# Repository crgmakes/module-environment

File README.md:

# Aquarius Environment Module

Environment monitoring module. Temperature, light, VOC, NOX, etc.

# Software 

You will need [KiCad](https://kicad.org) to view and edit this design. Click [here](https://www.kicad.org/download/) to download.

You will also need all the associated libraries and models to drive the design if you want to make changes or view the 3D rendering:

https://github.com/crgmakes/kicad-library.git

Kicad MUST be configured properly to use all the files in this repo. Once you have Kicad installed, under Preferences->Configure Paths..., make the following entries:

1 - KICAD_USER_DIR -> set to the root location of where you placed the above repository.
2 - KICAD_USER_LIBRARY = ${KICAD_USER_DIR}/Library
3 - KICAD_USER_MODEL_DIR = ${KICAD_USER_LIBRARY}/models
4 - KICAD_USER_TEMPLATE_DIR	= ${KICAD_USER_LIBRARY}/templates	

Kicad will operate mostly normally if these are not set properly. You will notice an issue when you view the PCB in 3D mode.

***NOTE***: after makeing a release build in git, if your rendered 3D images are missing components, ensure the path to EVERY component model is set to ${KICAD_USER_MODEL_DIR}/<model name>.

Kicad sometimes replaces the variable with an expansion and that FAILS during the build process because the expanded variable is local and does not match the build environment.

---

THE DESIGN IS PROVIDED "AS IS" AND THE AUTHOR DISCLAIMS ALL WARRANTIES WITH REGARD TO THIS DESIGN INCLUDING ALL IMPLIED WARRANTIES OF MERCHANTABILITY AND FITNESS. IN NO EVENT SHALL THE AUTHOR BE LIABLE FOR ANY SPECIAL, DIRECT, INDIRECT, OR CONSEQUENTIAL DAMAGES OR ANY DAMAGES WHATSOEVER RESULTING FROM LOSS OF USE, DATA OR PROFITS, WHETHER IN AN ACTION OF CONTRACT, NEGLIGENCE OR OTHER TORTIOUS ACTION, ARISING OUT OF OR IN CONNECTION WITH THE USE OR PERFORMANCE OF THIS DESIGN.

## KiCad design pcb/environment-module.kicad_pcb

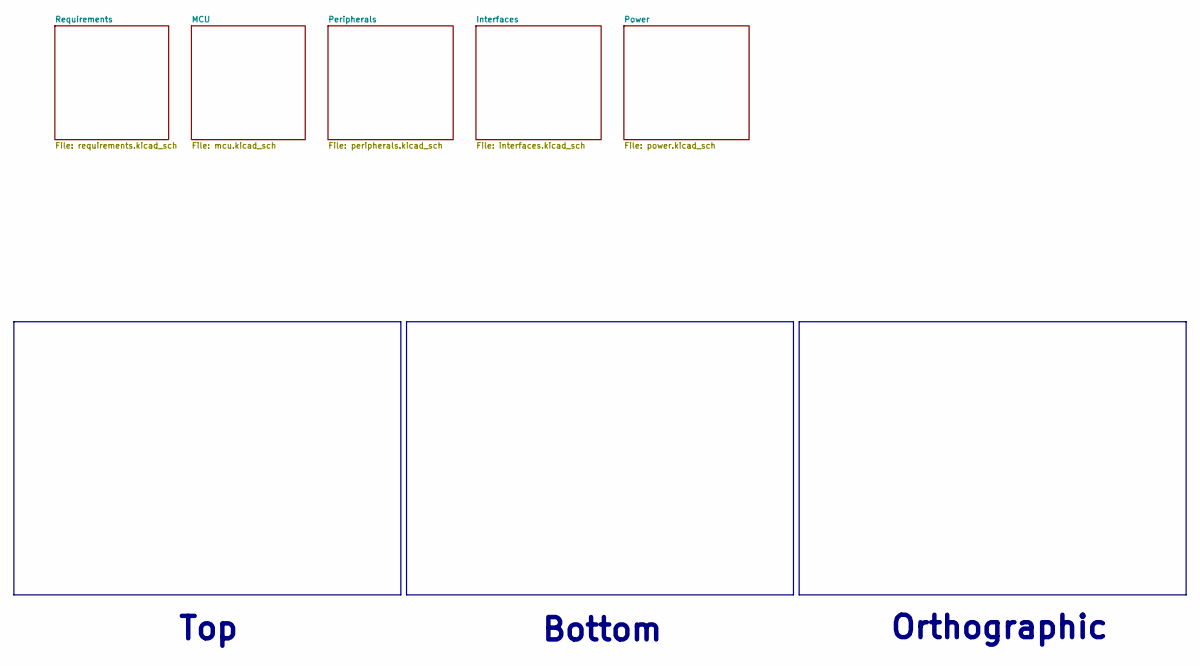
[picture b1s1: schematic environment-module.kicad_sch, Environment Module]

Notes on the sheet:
Bottom
Top
Orthographic

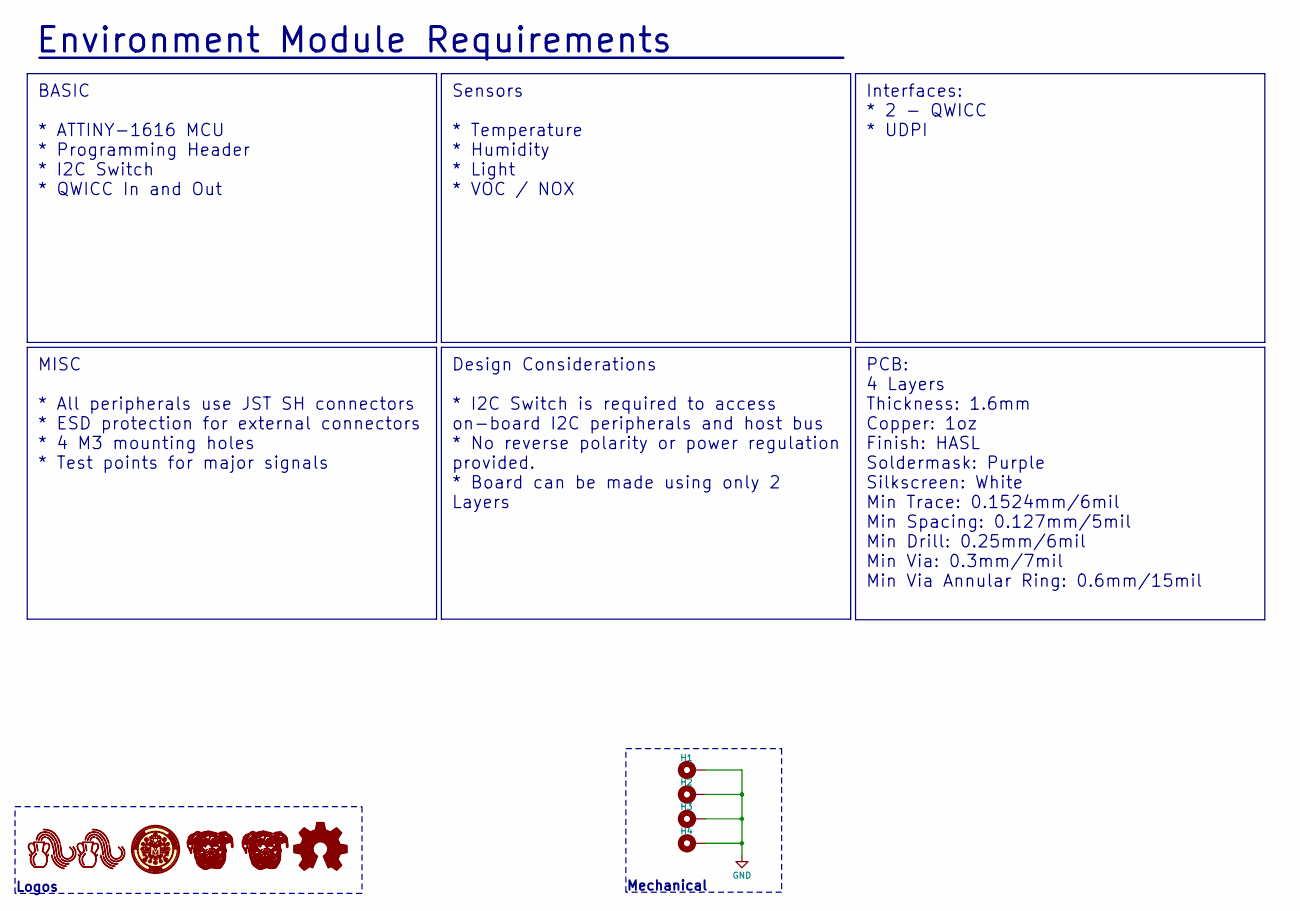
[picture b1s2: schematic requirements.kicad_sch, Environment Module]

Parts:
H1, H2, H3, H4: MountingHole_3.2mm_M3_Pad_Via
LOGO1, LOGO2: Aquarius Logo 5mm
LOGO3: CRGM Logo 7mm
LOGO4, LOGO5: Roxy 6.5mm
LOGO6: OSHW-Logo_5.7x6mm_SilkScreen

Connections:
GND: H1.1, H2.1, H3.1, H4.1; also elsewhere on the board

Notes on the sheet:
Logos
Environment Module Requirements
Mechanical
Interfaces: * 2 - QWICC * UDPI
PCB: 4 Layers Thickness: 1.6mm Copper: 1oz Finish: HASL Soldermask: Purple Silkscreen: White Min Trace: 0.1524mm/6mil Min Spacing: 0.127mm/5mil Min Drill: 0.25mm/6mil Min Via: 0.3mm/7mil Min Via Annular Ring: 0.6mm/15mil
BASIC * ATTINY-1616 MCU * Programming Header * I2C Switch * QWICC In and Out
MISC * All peripherals use JST SH connectors * ESD protection for external connectors * 4 M3 mounting holes * Test points for major signals
Sensors * Temperature * Humidity * Light * VOC / NOX
Design Considerations * I2C Switch is required to access on-board I2C peripherals and host bus * No reverse polarity or power regulation provided. * Board can be made using only 2 Layers

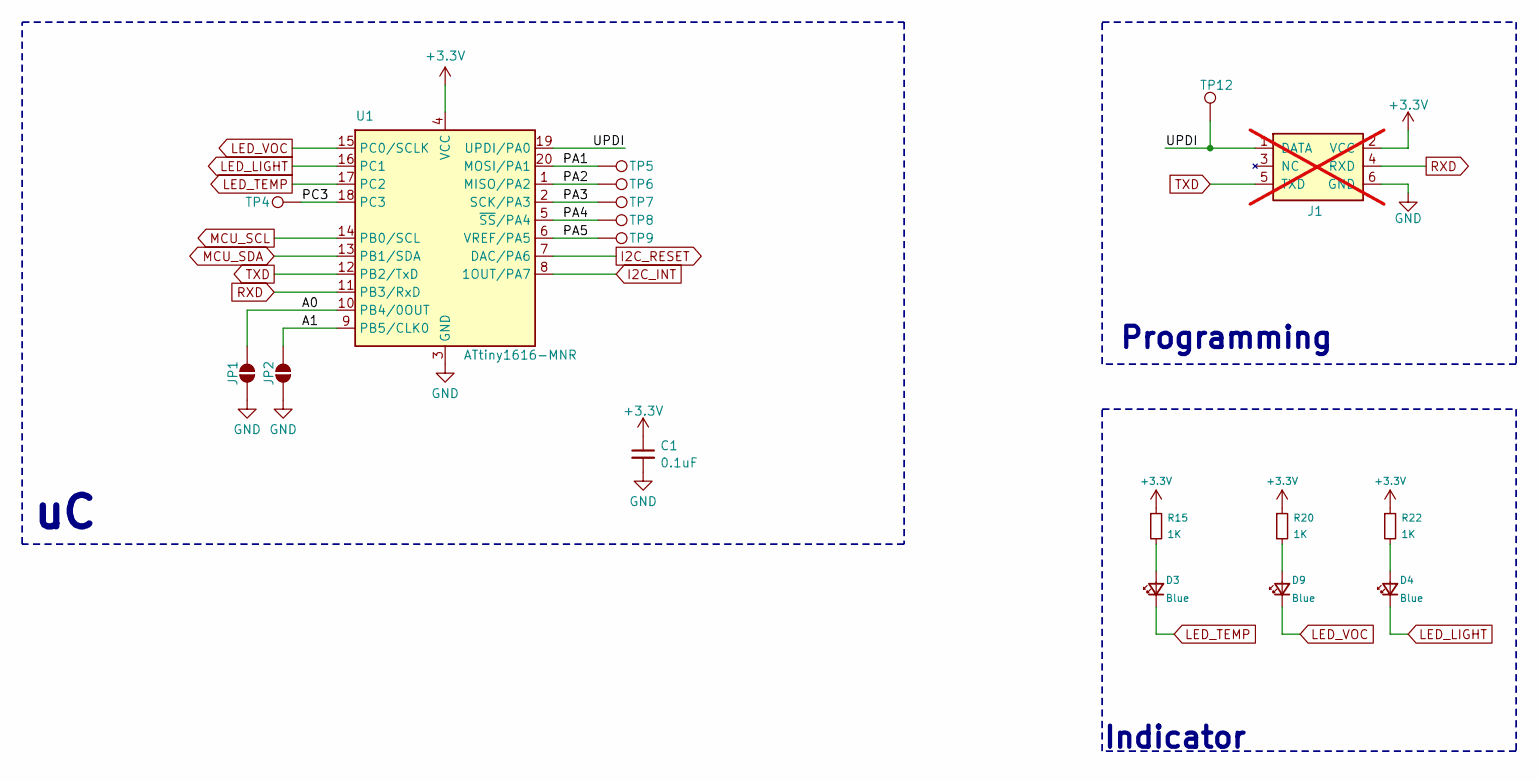
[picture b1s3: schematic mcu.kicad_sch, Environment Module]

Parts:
C1: 0.1uF; C_0603_1608Metric; Tolerance 10%; MPN CL10B104KO8NNNC; LCSC C66501
D3, D4, D9: Blue; LED_0603_1608Metric; MPN XL-1608UBC-04; Mouser 859-LTST-C190TBKT
J1: AVR-UPDI-6; PinHeader_2x03_P2.54mm_Vertical_SMD; not fitted
JP1, JP2: SolderJumper-2_P1.3mm_Open_RoundedPad1.0x1.5mm
R15, R20, R22: 1K; R_0603_1608Metric; Tolerance 5%; MPN FRC0603J102 TS; Mouser 71-CRCW06031K00JNEAC
TP4, TP5, TP6, TP7, TP8, TP9, TP12: TestPoint_Pad_D1.0mm
U1: ATtiny1616-MNR; VQFN-20-1EP_3x3mm_P0.4mm_EP1.7x1.7mm_ThermalVias; MPN ATTINY1616-MNR; Mouser 556-ATTINY1616MNR

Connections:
+3.3V: C1.1, J1.2 (VCC), R15.1, R20.1, R22.1, U1.4 (VCC); also elsewhere on the board
/MCU/A0: JP1.2 (B), U1.10 (PB4/0OUT)
/MCU/A1: JP2.2 (B), U1.9 (PB5/CLK0)
/MCU/PA1: TP5.1, U1.20 (MOSI/PA1)
/MCU/PA2: TP6.1, U1.1 (MISO/PA2)
/MCU/PA3: TP7.1, U1.2 (SCK/PA3)
/MCU/PA4: TP8.1, U1.5 (~SS/PA4)
/MCU/PA5: TP9.1, U1.6 (VREF/PA5)
/MCU/PC3: TP4.1, U1.18 (PC3)
/MCU/UPDI: J1.1 (DATA), TP12.1, U1.19 (UPDI/PA0)
GND: C1.2, J1.6 (GND), JP1.1 (A), JP2.1 (A), U1.3 (GND), U1.21 (GND); also elsewhere on the board
I2C_INT: U1.8 (1OUT/PA7); also elsewhere on the board
I2C_RESET: U1.7 (DAC/PA6); also elsewhere on the board
LED_LIGHT: D4.1 (K), U1.16 (PC1)
LED_TEMP: D3.1 (K), U1.17 (PC2)
LED_VOC: D9.1 (K), U1.15 (PC0/SCLK)
MCU_SCL: U1.14 (PB0/SCL); also elsewhere on the board
MCU_SDA: U1.13 (PB1/SDA); also elsewhere on the board
unnamed: D3.2 (A), R15.2
unnamed: D4.2 (A), R22.2
unnamed: D9.2 (A), R20.2
RXD: J1.4 (RXD), U1.11 (PB3/RxD)
TXD: J1.5 (TXD), U1.12 (PB2/TxD)

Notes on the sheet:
Programming
Indicator

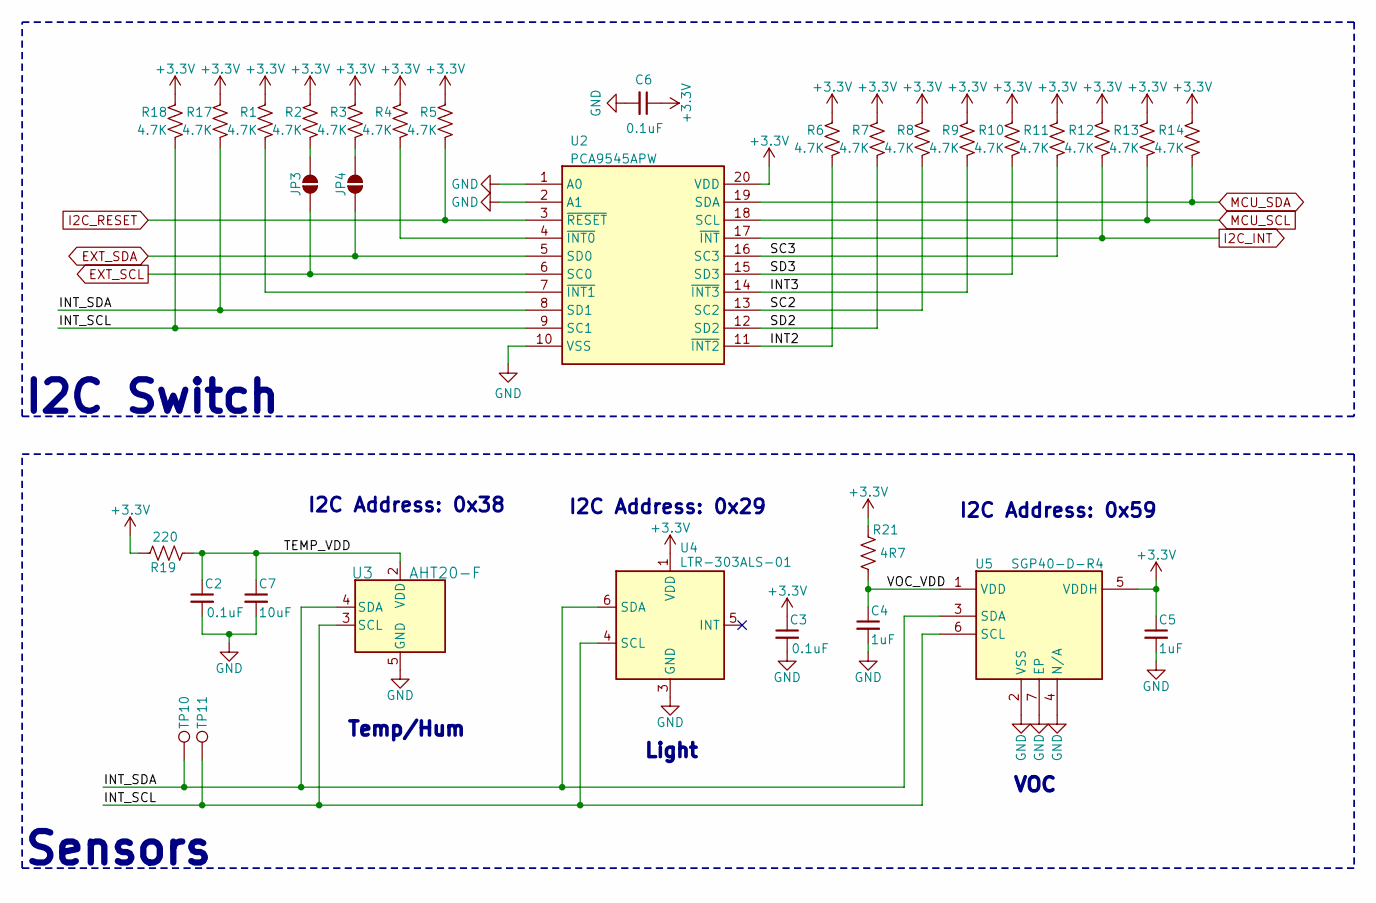
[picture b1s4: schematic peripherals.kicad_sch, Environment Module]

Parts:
C2, C3: 0.1uF; C_0603_1608Metric; Tolerance 10%; MPN CL10B104KO8NNNC; Digikey 1276-1005-2-ND
C4, C5: 1uF; C_0603_1608Metric; Tolerance 10%; MPN CGA0603X5R105K160JT; Mouser 187-CL10B105KO8NNNC
C6: 0.1uF; C_0603_1608Metric; Tolerance 10%; MPN CL10B104KO8NNNC; LCSC C66501
C7: 10uF; C_0603_1608Metric; Tolerance 10%; MPN CGA0603X5R106K100JT; Mouser 187-CL10A106KP8NNNC
JP3, JP4: SolderJumper-2_P1.3mm_Open_RoundedPad1.0x1.5mm
R1, R2, R3, R4, R5, R6, R7, R9, R10, R12, R13, R17, R18: 4.7K; R_0603_1608Metric; Tolerance 5%; MPN FRC0603J472 TS; Mouser 71-CRCW06034K70JNEAC
R8, R11, R14: 4.7K; R_0603_1608Metric; Tolerance 5%; MPN FRC0603J472 TS; LCSC C2907166
R19: 220; R_0603_1608Metric; Tolerance 5%; MPN FRC0603J221 TS; Mouser 652-CR0603JW-221ELF
R21: 4R7; R_0603_1608Metric; Tolerance 5%; MPN FRC0603J4R7 TS; Mouser 652-CR0603JW-4R7ELF
TP10, TP11: TestPoint_Pad_D1.0mm
U2: PCA9545APW; SOP65P640X110-20N; MPN PCA9545APW,118; Digikey 568-1865-2-ND
U3: AHT20-F; AHT20; MPN AHT20-F; LCSC C3012622
U4: LTR-303ALS-01; MPN LTR-303ALS-01; Digikey 160-2161-2-ND
U5: SGP40-D-R4; SON80P244X244X95-7N; MPN SGP40-D-R4; Digikey 1649-SGP40-D-R4TR-ND

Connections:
+3.3V: C3.1, C5.1, C6.1, R1.2, R2.2, R3.2, R4.2, R5.2, R6.2, R7.2, R8.2, R9.2, R10.2, R11.2, R12.2, R13.2, R14.2, R17.2, R18.2, R19.1, R21.1, U2.20 (VDD), U4.1 (VDD), U5.5 (VDDH); also elsewhere on the board
/Peripherals/INT2: R6.1, U2.11 (~INT2)
/Peripherals/INT3: R9.1, U2.14 (~INT3)
/Peripherals/INT_SCL: R18.1, TP11.1, U2.9 (SC1), U3.3 (SCL), U4.4 (SCL), U5.6 (SCL)
/Peripherals/INT_SDA: R17.1, TP10.1, U2.8 (SD1), U3.4 (SDA), U4.6 (SDA), U5.3 (SDA)
/Peripherals/SC2: R8.1, U2.13 (SC2)
/Peripherals/SC3: R11.1, U2.16 (SC3)
/Peripherals/SD2: R7.1, U2.12 (SD2)
/Peripherals/SD3: R10.1, U2.15 (SD3)
/Peripherals/TEMP_VDD: C2.1, C7.1, R19.2, U3.2 (VDD)
/Peripherals/VOC_VDD: C4.1, R21.2, U5.1 (VDD)
EXT_SCL: JP3.1 (A), U2.6 (SC0); also elsewhere on the board
EXT_SDA: JP4.1 (A), U2.5 (SD0); also elsewhere on the board
GND: C2.2, C3.2, C4.2, C5.2, C6.2, C7.2, U2.1 (A0), U2.2 (A1), U2.10 (VSS), U3.5 (GND), U4.3 (GND), U5.2 (VSS), U5.4 (N/A), U5.7 (EP); also elsewhere on the board
I2C_INT: R12.1, U2.17 (~INT); also elsewhere on the board
I2C_RESET: R5.1, U2.3 (~RESET); also elsewhere on the board
MCU_SCL: R13.1, U2.18 (SCL); also elsewhere on the board
MCU_SDA: R14.1, U2.19 (SDA); also elsewhere on the board
unnamed: JP3.2 (B), R2.1
unnamed: JP4.2 (B), R3.1
unnamed: R4.1, U2.4 (~INT0)
unnamed: R1.1, U2.7 (~INT1)

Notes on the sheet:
I2C Address: 0x29
I2C Address: 0x59
Light
Sensors
VOC
Temp/Hum
I2C Switch
I2C Address: 0x38

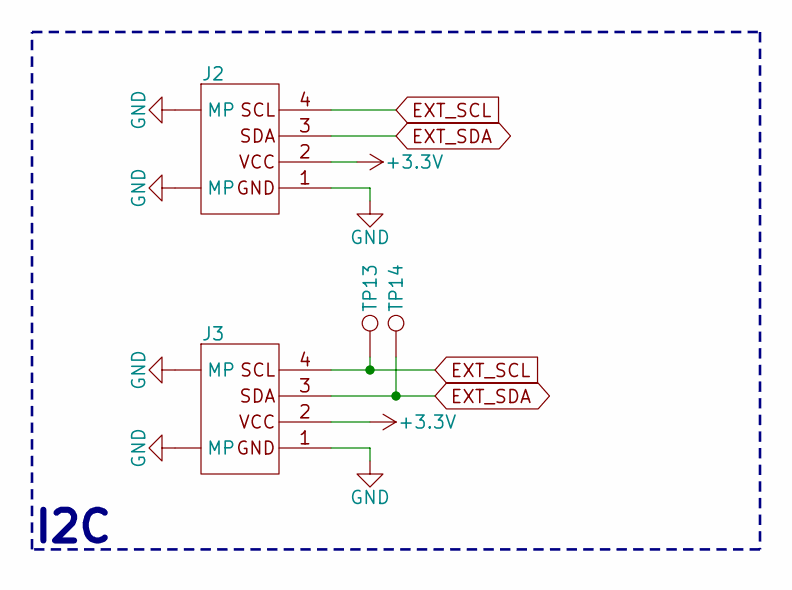
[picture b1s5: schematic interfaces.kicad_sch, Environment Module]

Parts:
J2, J3: JST_SH_BM04B-SRSS-TB_1x04-1MP_P1.00mm_Vertical; MPN BM04B-SRSS-TBT(LF)(SN); Mouser 306-BM04BSRSSTBTLFSN
TP13, TP14: TestPoint_Pad_D1.0mm

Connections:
+3.3V: J2.2, J3.2; also elsewhere on the board
EXT_SCL: J2.4, J3.4, TP13.1; also elsewhere on the board
EXT_SDA: J2.3, J3.3, TP14.1; also elsewhere on the board
GND: J2.0 (MP), J2.1, J2.5 (MP), J3.0 (MP), J3.1, J3.5 (MP); also elsewhere on the board

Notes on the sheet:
I2C

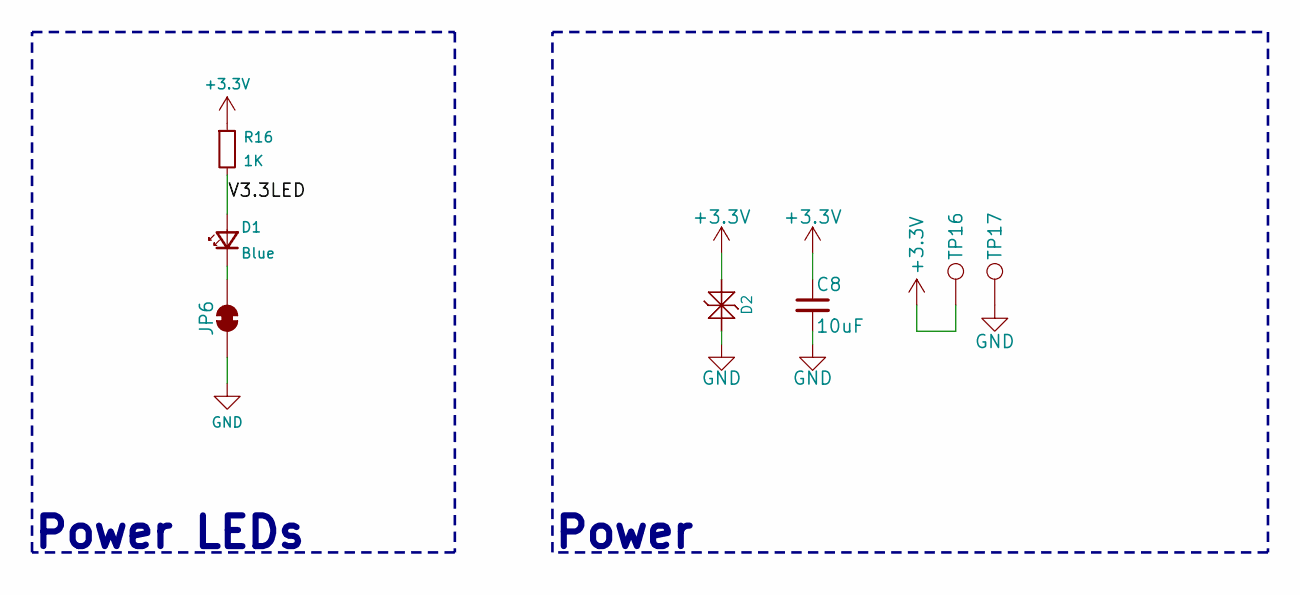
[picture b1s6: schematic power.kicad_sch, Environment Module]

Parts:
C8: 10uF; C_0603_1608Metric; Tolerance 10%; MPN CGA0603X5R106K100JT; Mouser 187-CL10A106KP8NNNC
D1: Blue; LED_0603_1608Metric; MPN XL-1608UBC-04; Mouser 859-LTST-C190TBKT
D2: PESD3V3S1BL; DFN1006-2; MPN LESD8D3.3CAT5G; LCSC C5563754
JP6: SolderJumper-2_P1.3mm_Bridged_RoundedPad1.0x1.5mm
R16: 1K; R_0603_1608Metric; Tolerance 5%; MPN FRC0603J102 TS; Mouser 71-CRCW06031K00JNEAC
TP16, TP17: TestPoint_Pad_D1.0mm

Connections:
+3.3V: C8.1, D2.2 (K2), R16.1, TP16.1; also elsewhere on the board
/Power/V3.3LED: D1.2 (A), R16.2
GND: C8.2, D2.1 (K1), JP6.1 (A), TP17.1; also elsewhere on the board
unnamed: D1.1 (K), JP6.2 (B)

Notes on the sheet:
Power LEDs
Power

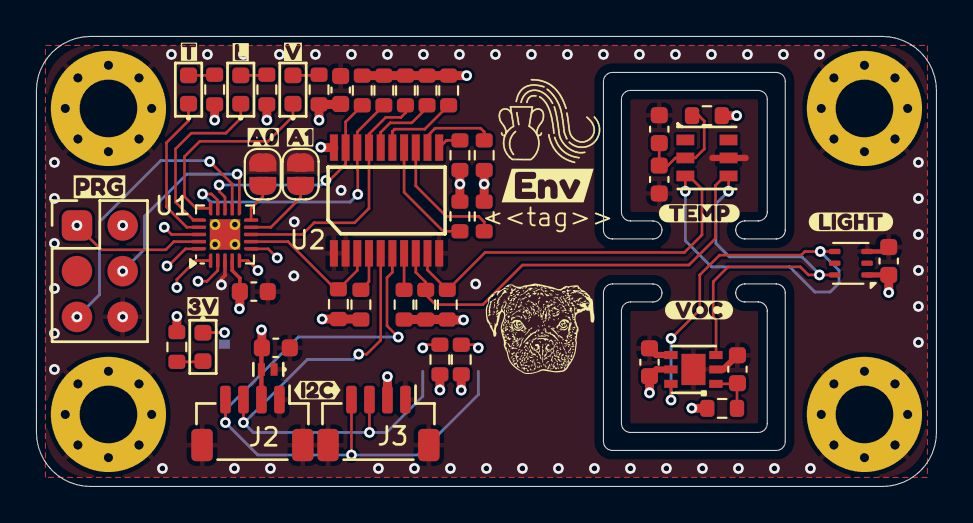
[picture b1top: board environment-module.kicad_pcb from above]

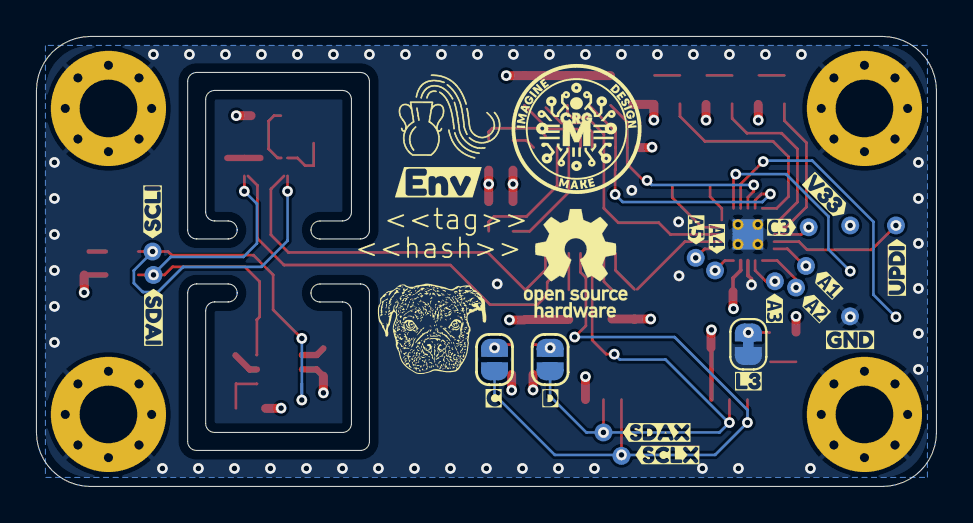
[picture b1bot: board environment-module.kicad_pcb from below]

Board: 4 copper layers, 50.0 x 25.0 mm, 100 parts (37 on the bottom side), 41 nets.

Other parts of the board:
kibuzzard-68F7F6D5: G***; kibuzzard-68F7F6D5
kibuzzard-68F7F6E1: G***; kibuzzard-68F7F6E1
kibuzzard-68FAFDB2: G***; kibuzzard-68FAFDB2
kibuzzard-68FAFDB8: G***; kibuzzard-68FAFDB8
kibuzzard-68FC4C70: G***; kibuzzard-68FC4C70
kibuzzard-69C852DC: G***; kibuzzard-69C852DC
kibuzzard-69C852F0: G***; kibuzzard-69C852F0
kibuzzard-69DC4F1F: G***; kibuzzard-69DC4F1F
kibuzzard-69DC4F14: G***; kibuzzard-69DC4F14
kibuzzard-69DC4F46: G***; kibuzzard-69DC4F46
kibuzzard-69DC53A1: G***; kibuzzard-69DC53A1
kibuzzard-69DC5370: G***; kibuzzard-69DC5370
kibuzzard-69DEF070: G***; kibuzzard-69DEF070
kibuzzard-690A7D98: G***; kibuzzard-690A7D98
kibuzzard-690D67E0: G***; kibuzzard-690D67E0
kibuzzard-690D683A: G***; kibuzzard-690D683A
kibuzzard-690D6815: G***; kibuzzard-690D6815
kibuzzard-690D6835: G***; kibuzzard-690D6835
kibuzzard-691D233B: G***; kibuzzard-691D233B
kibuzzard-6902B41D: G***; kibuzzard-6902B41D
kibuzzard-6902BBCC: G***; kibuzzard-6902BBCC
kibuzzard-6908DD87: G***; kibuzzard-6908DD87
kibuzzard-6952D1DF: G***; kibuzzard-6952D1DF
kibuzzard-6952D1FF: G***; kibuzzard-6952D1FF
kibuzzard-6952D20C: G***; kibuzzard-6952D20C
kibuzzard-69029C60: G***; kibuzzard-69029C60
kibuzzard-69571EBA: G***; kibuzzard-69571EBA
kibuzzard-69571EDB: G***; kibuzzard-69571EDB
kibuzzard-69571F0B: G***; kibuzzard-69571F0B

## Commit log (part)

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2025-10-30 Initial check in
2025-11-02 Fixed LTR address from 0x80 to 0x40
2025-11-03 Updates for consistency
    Changed mounting holes to grounded
    Updated power connectors
    Added power ESD protection
2025-11-03 Swapped temp sensor for more popular model
    Changed HDC1080 for AHT20
    Updated reference layer
    Updated renders
    Updated requirements
    Fixed models
2025-11-04 Switched back to global lables
    Updated all gnd and test point symbols
2025-11-04 Updates for DFM
2025-11-04 Renamed to be consistent with other modules
2025-11-04 Updated footprints for DFM
2025-11-04 Updated for DFM
    Cleaned up board
    Updated footprints
    Adjusted silkscreen
    Fixed panel options name
    Changed project name
2025-11-05 Updated silkscreen
2025-11-07 clean up and final processing
2025-11-07 Fixed model paths
2025-11-19 Fixed sillkscreen and renders
2025-12-27 Moved sensors to edge of board
    Adjusted routing and silkscreen
2025-12-28 Changed I2C to open instead of bridged
    Moved I2C jumper to back
    Changed to open instead of bridged
    Changed Roxy to 5mm on front
    Moved silkscreen around.
    Updated renders
    Removed logos from BOM
2025-12-29 Added labels for sensors
    Fixed part numbers for connectors
    Remove unnecessary property values
2025-12-29 Updated fab layer references
2026-01-02 Redesign with cutouts for sensors
    Removed power connectors since 5V is not needed
    Added cutout for VOC sensor
    Rerouted sensor section
    Rescaled logos and fixed silkscreen
    Changed to blue LED for power indicator
    Updated requirements and renders
2026-01-03 Removed FNWW logo
    Adjusted silkscreen on back
2026-03-01 replaced .wrl with .step
2026-04-13 Updated UPDI Connector
    Integrated serial and UPDI
    Changed to vertical connectors
    Updated renders
    Rounded cutouts
    Adjusted silkscreen
2026-04-13 Closed #3
    Added status LEDs -- updated
    Updated renders
    Updated silkscreen
2026-04-15 Changed to inside cutouts
    Updated renders
    Increased size of Roxy on front ❤️
2026-04-15 Rounded cutouts
    Updated renders
2026-04-15 Changed post radius to 0.1mm
    No internal cutouts with a 'normal' sized radius.
2026-04-15 Removed mill radius and added outer
    Fixes panel frame radius problems.
2026-04-15 Adjusted spacing and alignment of parts
    Moved temp and voc to be on grid
    Updated renders
    Ran ERC -- fixed errors
    Ran DRC -- fixed errors
